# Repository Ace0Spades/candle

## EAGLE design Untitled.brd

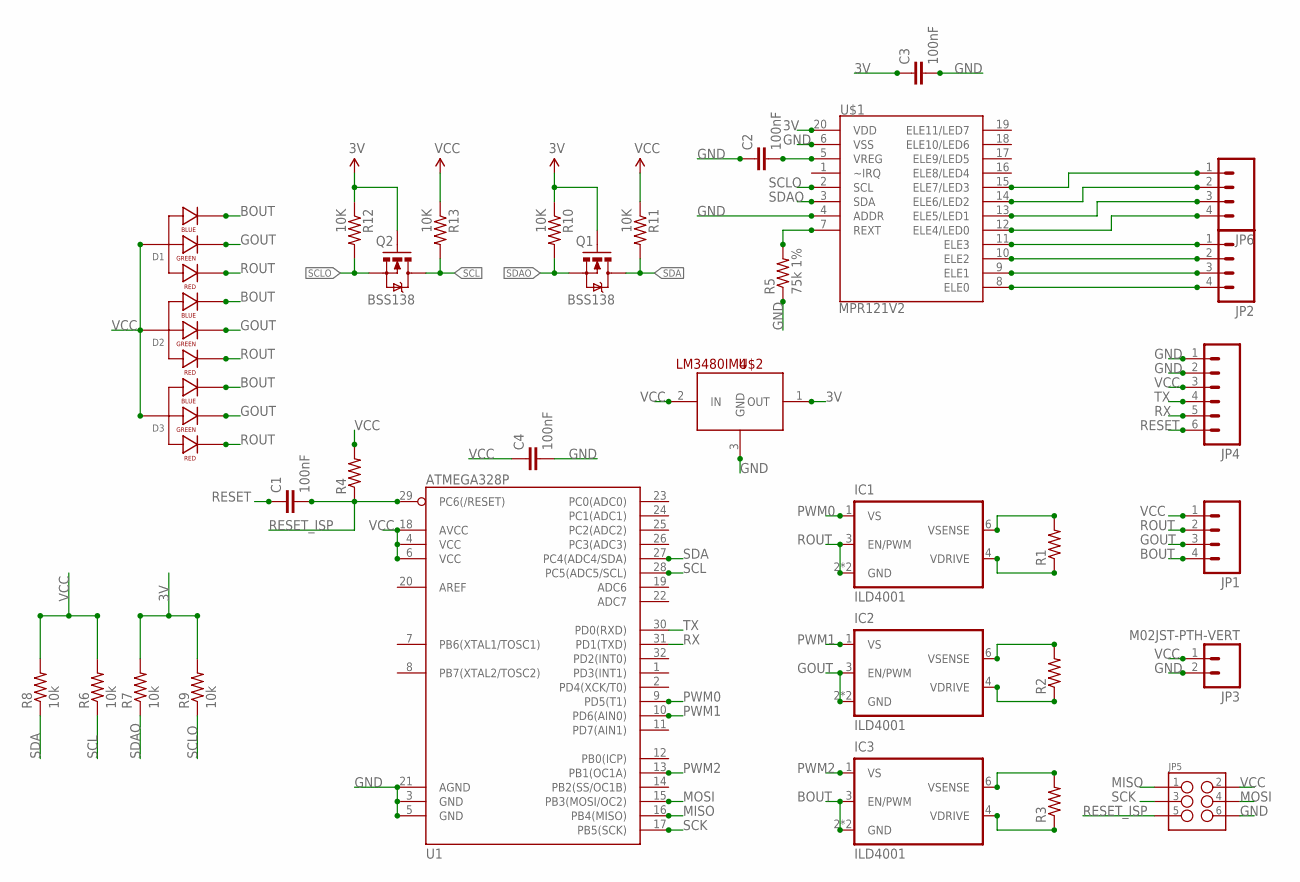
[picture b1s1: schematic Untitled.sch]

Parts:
C1, C2, C3, C4: 100nF; 0805
D1, D2, D3: LED-RGB-CA-THRUCLEAR; LED-RGB-THRU
IC1, IC2, IC3: ILD4001; SC74_INFINEON
JP1, JP2, JP6: M04JST-PTH-VERT; JST-4-PTH-VERT
JP3: M02JST-PTH-VERT; JST-2-PTH-VERT
JP4: M06LONGPADS; 1X06_LONGPADS
JP5: M03X22X3_SILK_MALE_PTH; 2X3
Q1, Q2: BSS138; SOT23-3
R1, R2, R3, R4: RESISTOR0805-RES; 0805
R5: 75k 1%; 0805
R6, R7, R8, R9: 10k; 0805
R10, R11, R12, R13: 10K; 0603-RES
U1: ATMEGA328P; TQFP32-08
U$1: MPR121V2; QFN-20-0.4MM-V2
U$2: LM3480IM4; SOT23-3

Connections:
3V: C3.1, Q1.1 (G), Q2.1 (G), R7.2, R9.2, R10.1, R12.1, U$1.20 (VDD), U$2.1 (OUT)
BOUT: D1.4 (BLUE_CATHODE), D2.4 (BLUE_CATHODE), D3.4 (BLUE_CATHODE), IC3.2 (GND), IC3.3 (EN/PWM), IC3.5 (GND), JP1.4
GND: C2.1, C3.2, C4.2, JP3.2, JP4.1, JP4.2, JP5.6, R5.1, U1.3 (GND), U1.5 (GND), U1.21 (AGND), U$1.4 (ADDR), U$1.6 (VSS), U$2.3 (GND)
GOUT: D1.3 (GREEN_CATHODE), D2.3 (GREEN_CATHODE), D3.3 (GREEN_CATHODE), IC2.2 (GND), IC2.3 (EN/PWM), IC2.5 (GND), JP1.3
MISO: JP5.1, U1.16 (PB4(MISO))
MOSI: JP5.4, U1.15 (PB3(MOSI/OC2))
unnamed: JP2.1, U$1.11 (ELE3)
unnamed: JP2.2, U$1.10 (ELE2)
unnamed: JP2.3, U$1.9 (ELE1)
unnamed: JP2.4, U$1.8 (ELE0)
unnamed: JP6.4, U$1.12 (ELE4/LED0)
unnamed: JP6.3, U$1.13 (ELE5/LED1)
unnamed: IC1.6 (VSENSE), R1.2
unnamed: IC1.4 (VDRIVE), R1.1
unnamed: IC2.6 (VSENSE), R2.2
unnamed: IC2.4 (VDRIVE), R2.1
unnamed: IC3.6 (VSENSE), R3.2
unnamed: IC3.4 (VDRIVE), R3.1
unnamed: JP6.2, U$1.14 (ELE6/LED2)
unnamed: JP6.1, U$1.15 (ELE7/LED3)
unnamed: R5.2, U$1.7 (REXT)
unnamed: C2.2, U$1.5 (VREG)
PWM0: IC1.1 (VS), U1.9 (PD5(T1))
PWM1: IC2.1 (VS), U1.10 (PD6(AIN0))
PWM2: IC3.1 (VS), U1.13 (PB1(OC1A))
RESET: C1.1, JP4.6
RESET_ISP: C1.2, JP5.5, R4.1, U1.29 (PC6(/RESET))
ROUT: D1.1 (RED_CATHODE), D2.1 (RED_CATHODE), D3.1 (RED_CATHODE), IC1.2 (GND), IC1.3 (EN/PWM), IC1.5 (GND), JP1.2
RX: JP4.5, U1.31 (PD1(TXD))
SCK: JP5.3, U1.17 (PB5(SCK))
SCL: Q2.3 (D), R6.1, R13.2, U1.28 (PC5(ADC5/SCL))
SCLO: Q2.2 (S), R9.1, R12.2, U$1.2 (SCL)
SDA: Q1.3 (D), R8.1, R11.2, U1.27 (PC4(ADC4/SDA))
SDAO: Q1.2 (S), R7.1, R10.2, U$1.3 (SDA)
TX: JP4.4, U1.30 (PD0(RXD))
VCC: C4.1, D1.2 (ANODE), D2.2 (ANODE), D3.2 (ANODE), JP1.1, JP3.1, JP4.3, JP5.2, R4.2, R6.2, R8.2, R11.1, R13.1, U1.4 (VCC), U1.6 (VCC), U1.18 (AVCC), U$2.2 (IN)

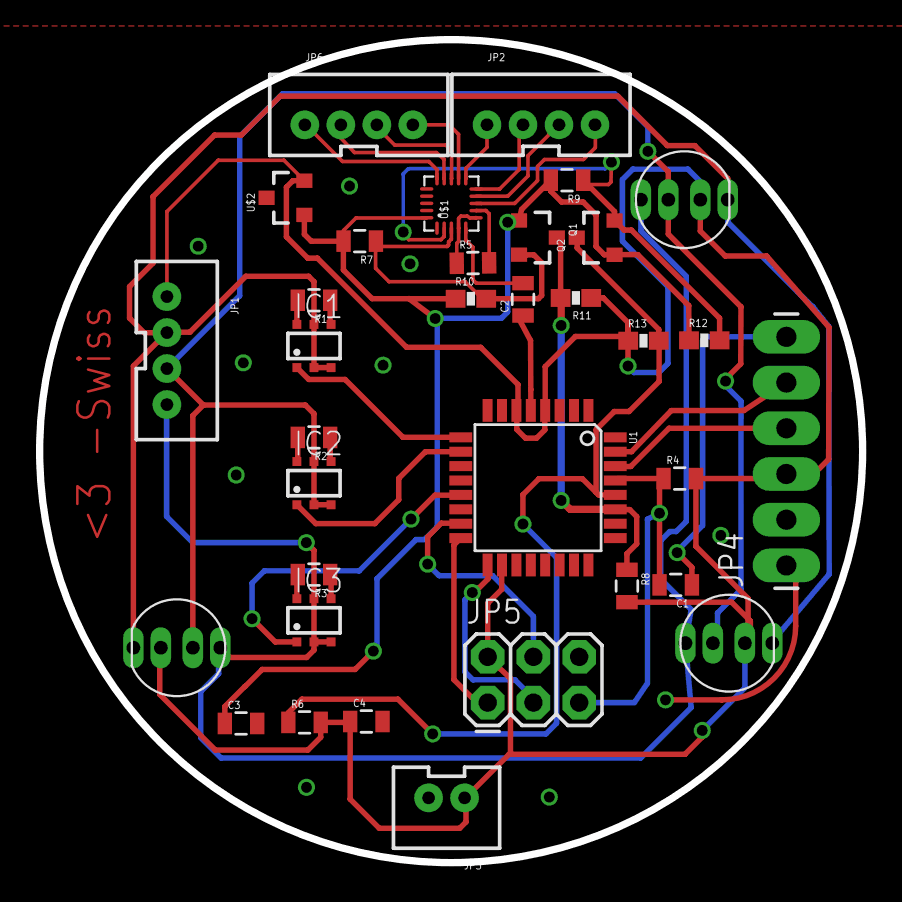
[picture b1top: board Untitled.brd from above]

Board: 2 copper layers, 45.7 x 45.7 mm, 34 parts (0 on the bottom side), 36 nets.

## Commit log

2015-02-18 :neckbeard: Added .gitattributes & .gitignore files
2015-03-17 initial
2015-03-17 almost done
2015-03-18 rev1
2015-04-28 Fixed RGB LED spacing
    RGB LEDs now have spaces between pads. Added 4 capacitive sense channel
    breakouts.
2015-06-20 Fixed unidirectional buffer and added missing connections to mpr121
2015-06-22 Added resistors
2015-07-04 changed level shifter
    changed the 5v -> 3v level shifters out for mossiest and changed the
    board to support them.

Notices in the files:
parts and their libraries:
SparkFun-DigitalIC: Licensing: Creative Commons ShareAlike 4.0 International - https://creativecommons.org/licenses/by-sa/4.0
